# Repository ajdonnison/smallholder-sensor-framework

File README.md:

The Small Holding Sensor Framework is a collection of arduino code,
hardware designs and server software to manage a sensor collection
in an intelligent manner.

It is specifically designed for small holdings, hobby farms, etc,
but is equally applicable to larger properties, industry and homes.

Currently the range of controllers include:

* Motion Sensing Light
* Brooder Temperature Control
* General Purpose Temperature Control
* Greywater Control
* Solar Hot Water Control
* Temperature Management for Chicken Coops
* Tank Depth Sensing

Each of these was designed for a problem at hand and is in current
use.

Virtually all of the devices use the Arduino Pro Mini or
compatible. Originaly using the Digi XBee, now mostly settled on
the NRF24L+ low-cost radio modules.

Most work recently is on creating a generic sensor that can be adapted
to most situations.  This has been based on the General Purpose Temperature
Controller, and in its first incarnation is used to manage either one or
two temperature sensors for either heating or cooling.  This has now
supplanted the Brooder Temperature Control, General Purpose Temperature
Control, Solar Hot Water Control and is being usd in all of these situations
as well as managing a Solar ceiling cooler.  The idea is to get this down
to a few small boards that can be replicated easily for differing purposes.

Arduino libraries required:

* DHT22
* PciManager
* SoftTimer
* DallasTemperatureControl
* OneWire

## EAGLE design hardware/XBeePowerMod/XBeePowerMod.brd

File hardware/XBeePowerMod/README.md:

# XBee Power Level Shifter

Based on the [SparkFun level shifter](https://www.sparkfun.com/products/11978) this was designed to handle level shifting and voltage control for the XBee.  I see that SparkFun have now introduced [something very similar](https://www.sparkfun.com/products/11373), with a far better footprint.

This includes the Eagle board and schematic files.

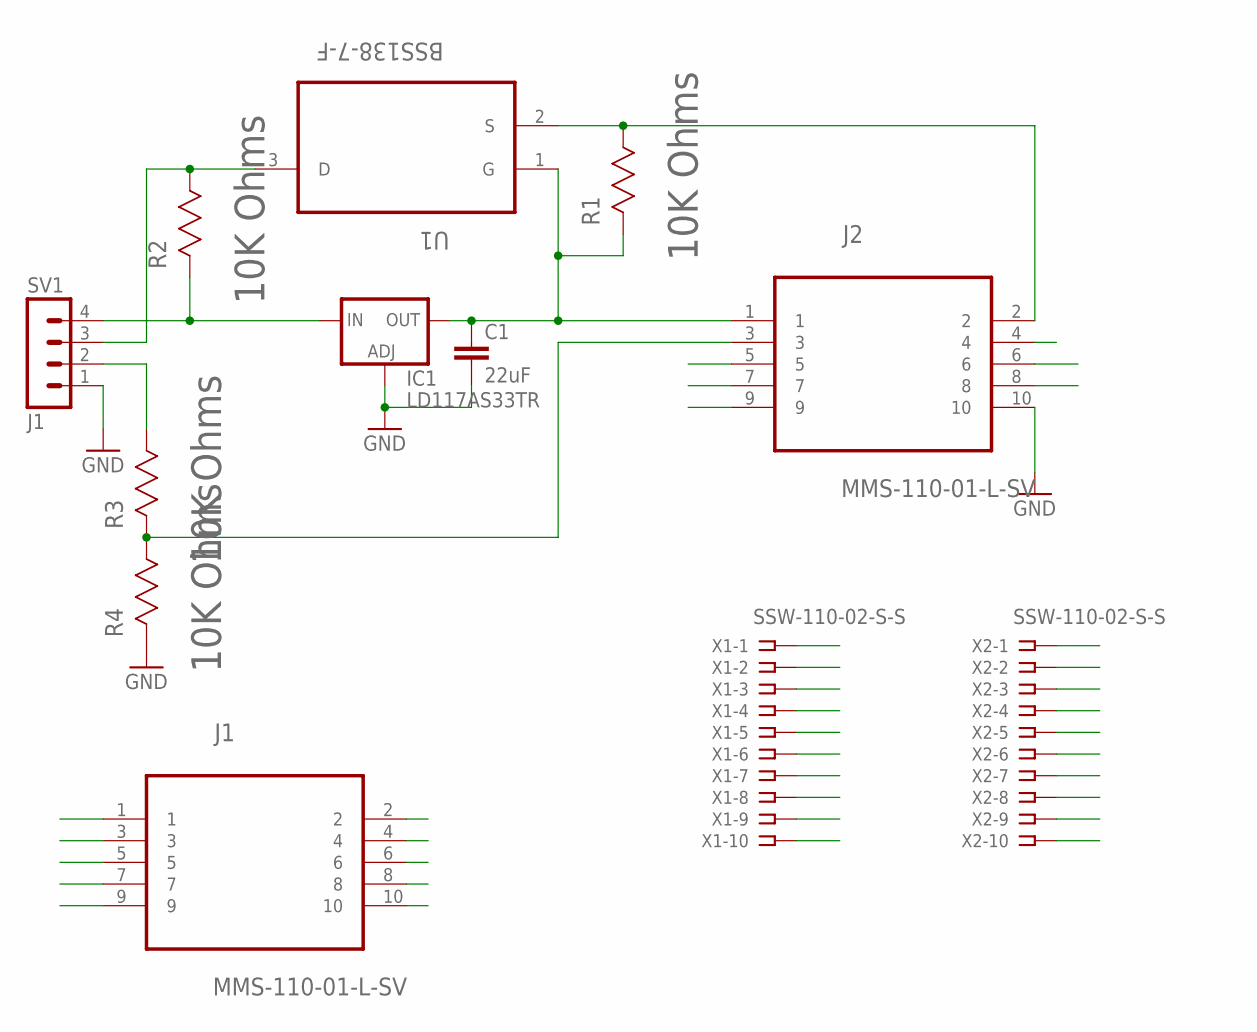
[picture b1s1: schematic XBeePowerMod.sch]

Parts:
C1: 22uF; C1206K
IC1: LD117AS33TR; SOT223
J1, J2: MMS-110-01-L-SV; SAMTEC_MMS-110-01-L-SV
R1, R2, R3, R4: 10K Ohms; RESC3216X71N
SV1: J1; MA04-1
U1: BSS138-7-F; SOT95P240X110-3N
X1, X2: SSW-110-02-S-S

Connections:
GND: C1.2, IC1.1 (ADJ), J2.10, R4.2 (R2), SV1.1, X2.10
unnamed: IC1.3 (IN), R2.2 (R2), SV1.4
unnamed: R3.1 (R1), SV1.2
unnamed: R2.1 (R1), SV1.3, U1.3 (D)
X10: J1.10, X1.10
X11: J1.1, X1.1
X12: J1.2, X1.2
X13: J1.3, X1.3
X14: J1.4, X1.4
X15: J1.5, X1.5
X16: J1.6, X1.6
X17: J1.7, X1.7
X18: J1.8, X1.8
X19: J1.9, X1.9
X21: C1.1, IC1.4 (OUT), J2.1, R1.2 (R2), U1.1 (G), X2.1
X22: J2.2, R1.1 (R1), U1.2 (S), X2.2
X23: J2.3, R3.2 (R2), R4.1 (R1), X2.3
X24: J2.4, X2.4
X25: J2.5, X2.5
X26: J2.6, X2.6
X27: J2.7, X2.7
X28: J2.8, X2.8
X29: J2.9, X2.9

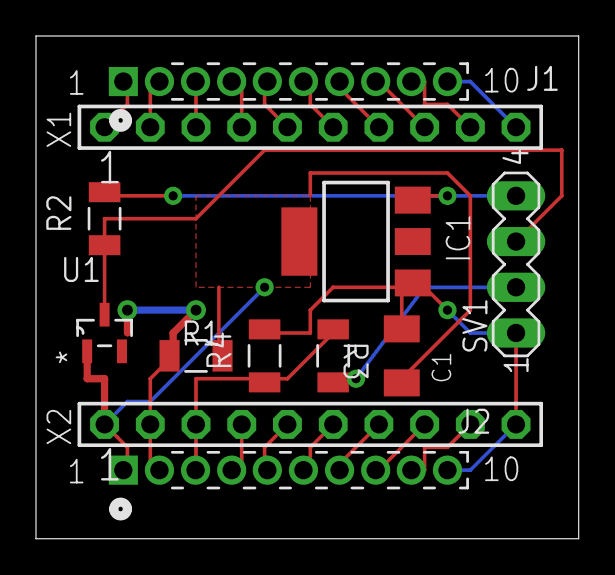
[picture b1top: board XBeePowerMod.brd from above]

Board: 2 copper layers, 30.2 x 27.9 mm, 12 parts (0 on the bottom side), 23 nets.

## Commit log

2014-02-09 Initial commit of Small Holdings Sensor Framework
2014-02-09 Added readme
2014-02-09 Updated comments in Arduino sketches.
2014-02-09 Fixed markdown in readme
2014-02-09 Fix modelines, provide README docs
2014-02-09 Added XBee interface board
2014-02-09 Updated as to current status of Wattworks.
2014-02-09 More readme files.
2014-02-26 Tidy up config file handling.
2014-02-26 Added debug mode to water heater
    To bench test without connecting up the temperature sensors
    this debug code adds the ability to manually trigger the
    relay.
2014-03-01 Add sensor scan and error detect
    Adds an extra button to initiate a bus scan for the temp sensors,
    writes this to EEPROM. Uses on-board LED to indicate error if
    no sensors found or addresses invalid.
    Changed to use SoftTimer library for blink/scan/check functions.
2014-04-29 Set indicator, remove startup test.
2014-04-29 Changed to display based multi-pupose controller
2014-04-29 Added hacked LedControl library
2014-04-30 Added status messages.
2014-04-30 Changed start message.
2014-05-02 Tidy up, make setup logic more sane.
2014-05-02 Ensure keypress event is cleared on keyup.
2014-05-02 Fix error message
2014-08-29 Experimental radio sensor module
2014-09-05 Scaffold of RF24 networked sensor.
2014-09-28 Added external config header, 2nd relay
2014-12-20 Network sensor support
    Added hacked Eagle library for Chinese clone Pro Mini
    Changed setup to match new standardised board layout
    Added library for the EEPROM on the TinyRTC board
2014-12-20 Clean up serial output.
2014-12-23 Make sure address is set between block reads.
2014-12-23 Add temperature sensor support and more debug
2015-01-13 Add basic network capabilities, display
2015-01-13 Add network message handling.
2015-01-15 Move configuration to radio interface.
2015-02-21 Fixed handling when no display involved.
2015-02-22 Check network after send, handle mode config
2015-09-14 Allow radio address to be set
2015-09-15 Multiple changes to support different configs
    Added HAS_EEPROM and HAS_RTC defines to support simpler configs.
    Made sure temperature sensor discovery is run when no stored config.
    Updated to latest version of RF24 libraries.
2015-09-15 Discover sensors when display first fires.
2015-09-16 Updated doco
2015-09-22 More config moved into setup.h
2015-09-22 Use Radio address as seed to create backoff
2015-09-22 More autonomy for setup, rationalise functions
2015-09-22 Update doco
2015-09-23 Fixes for setting temp, address.
2015-09-30 Restructure and tidy up to extend usability
2015-11-05 Optimise memory usage.
2017-01-29 Replace sensor.
2017-01-29 Add debug/test menu
2017-11-17 Cleanup of Network Sensor
2017-11-19 Add auto-discovery of sensors, config menu.
2017-12-02 Fix off-by-one error, make max temp configurable
2018-01-21 Make radio configurable, enable onboard EEPROM
    Radio is now configurable with HAS_RADIO in setup.cfg. The
    HAS_EEPROM now determines if an external EEPROM or the onboard
    EEPROM is used.
2018-02-17 TZ handling, faster respose, handle new sensors
2018-11-08 Fix test mode offset.
2023-01-14 Expand configs, fully detail menu options
2024-02-03 Make sure struct matches usage
2024-12-14 Add min-temp, fix handling of timings
2024-12-15 Make sure we display the min temp in config
2025-01-09 Update README for Mister to match latest usage
